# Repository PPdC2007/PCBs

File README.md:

# PCBs
Projects of Printed Circuit Boards made through Kicad.

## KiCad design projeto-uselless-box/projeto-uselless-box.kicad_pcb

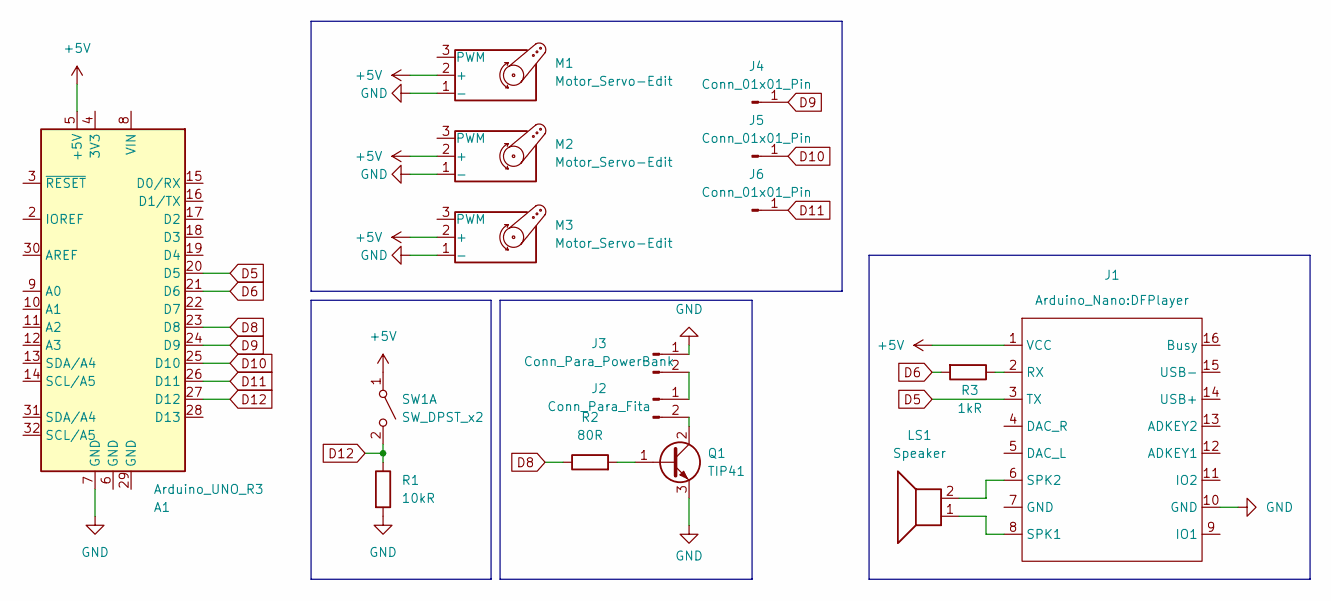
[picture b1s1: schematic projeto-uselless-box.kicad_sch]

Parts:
A1: Arduino_UNO_R3
J1: DFPlayer
J2: Conn_Para_Fita; TerminalBlock_Phoenix_MKDS-1,5-2-5.08_1x02_P5.08mm_Horizont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
J3: Conn_Para_PowerBank; TerminalBlock_Phoenix_MKDS-1,5-2-5.08_1x02_P5.08mm_Horizont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
J4, J5, J6: Conn_01x01_Pin; PinSocket_1x01_P2.54mm_Vertical
LS1: Speaker; TerminalBlock_Phoenix_MKDS-1,5-2-5.08_1x02_P5.08mm_Horizont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
M1, M2, M3: Motor_Servo-Edit; PinSocket_1x02_P2.54mm_Vertical
Q1: TIP41; TO-220-3_Vertical
R1: 10kR; R_Axial_DIN0207_L6.3mm_D2.5mm_P10.16mm_Horizontal
R2: 80R; R_Axial_DIN0207_L6.3mm_D2.5mm_P10.16mm_Horizontal
R3: 1kR; R_Axial_DIN0207_L6.3mm_D2.5mm_P10.16mm_Horizontal
SW1: SW_DPST_x2; TerminalBlock_Phoenix_MKDS-1,5-2-5.08_1x02_P5.08mm_Horizont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

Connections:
+5V: A1.5 (+5V), J1.1 (VCC), M1.2 (+), M2.2 (+), M3.2 (+), SW1.1 (A)
D5: A1.20 (D5), J1.3 (TX)
D6: A1.21 (D6), R3.2
D8: A1.23 (D8), R2.1
D9: A1.24 (D9), J4.1
D10: A1.25 (D10), J5.1
D11: A1.26 (D11), J6.1
D12: A1.27 (D12), R1.1, SW1.2 (B)
GND: A1.7 (GND), J1.10 (GND), J3.1, M1.1 (-), M2.1 (-), M3.1 (-), Q1.3 (E), R1.2
unnamed: J1.2 (RX), R3.1
unnamed: J1.8 (SPK1), LS1.1
unnamed: J1.6 (SPK2), LS1.2
unnamed: J2.1, J3.2
unnamed: J2.2, Q1.2 (C)
unnamed: Q1.1 (B), R2.2

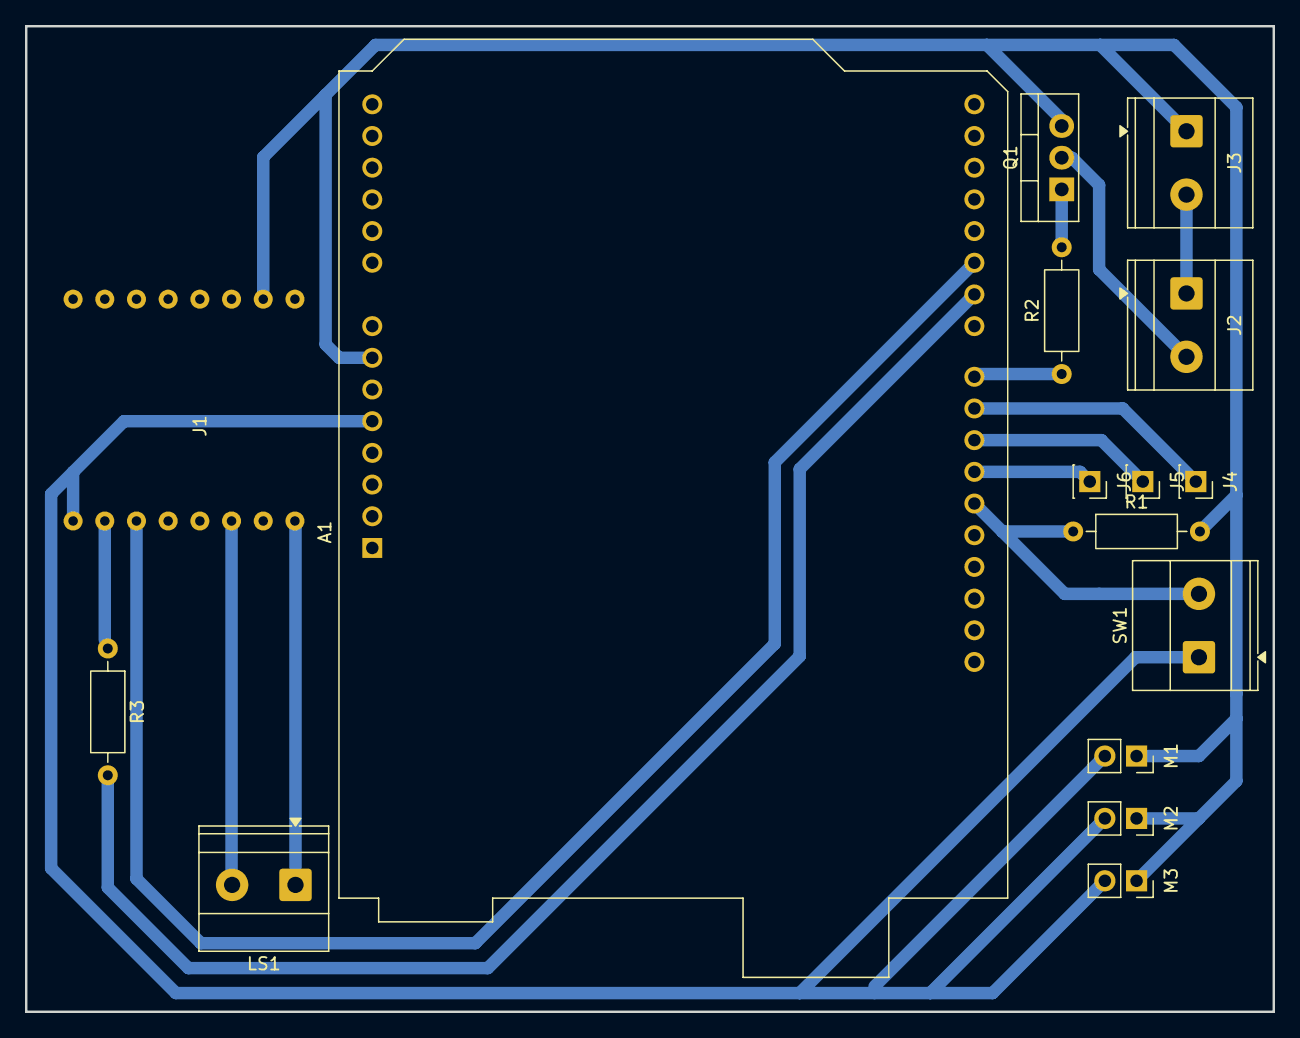
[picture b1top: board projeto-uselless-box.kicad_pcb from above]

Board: 2 copper layers, 100.0 x 79.0 mm, 16 parts (0 on the bottom side), 15 nets.
